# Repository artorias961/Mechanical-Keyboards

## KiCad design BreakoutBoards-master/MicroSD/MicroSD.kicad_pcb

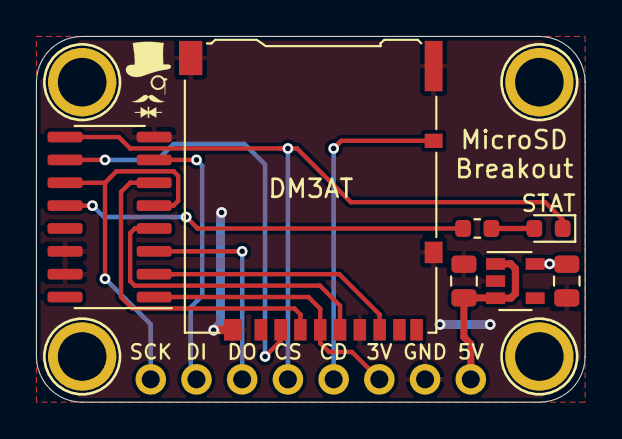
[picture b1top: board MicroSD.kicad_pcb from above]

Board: 2 copper layers, 30.5 x 20.3 mm, 12 parts (1 on the bottom side), 14 nets.

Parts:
C1, C2: 10uF; C_0805_2012Metric
DM3AT: Micro_SD_Card_Det; microSD_HC_Hirose_DM3AT-SF-PEJM5
H1, H2, H3, H4: MountingHole; MountingHole_M2.5_SirBoard
J1: Conn_01x08; PinHeader_1x08_P2.54mm_Vertical
R6: 1K; R_0603_1608Metric
STAT: LED; LED_0603_1608Metric
U1: AP2127K-3.3; SOT-23-5
U2: 4050; SOIC-16_3.9x9.9mm_P1.27mm

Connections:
/CLK_SD: DM3AT.5, U2.4
/CS_SD: DM3AT.2, U2.10
/DI_SD: DM3AT.3, U2.6
/DO_SD: DM3AT.7, U2.2
CS: J1.4, STAT.1, U2.9
DETA: DM3AT.10, J1.5
DI: J1.2, U2.7
DO: J1.3, U2.3
GND: C1.2, C2.2, DM3AT.6, DM3AT.11, J1.7, U1.2, U2.8, U2.14, U2.15
unnamed: R6.2, STAT.2
unnamed: R6.1, U2.12
SCK: J1.1, U2.5, U2.11
VIN: C1.1, J1.8, U1.1, U1.3
VOUT: C2.1, DM3AT.4, J1.6, U1.5, U2.1

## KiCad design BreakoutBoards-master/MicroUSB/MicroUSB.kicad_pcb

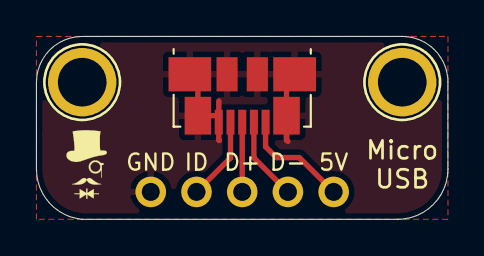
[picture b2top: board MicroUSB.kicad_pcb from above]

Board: 2 copper layers, 22.9 x 10.2 mm, 4 parts (1 on the bottom side), 5 nets.

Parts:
H1, H2: MountingHole; MountingHole_M2.5_SirBoard
J1: USB_B_Micro; USB_Micro-B_Molex_47346-0001
J2: Conn_01x05; PinHeader_1x05_P2.54mm_Vertical

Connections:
/D+: J1.3, J2.3
/D-: J1.2, J2.2
/GND: J1.5, J1.6, J2.5
/ID: J1.4, J2.4
/VBus: J1.1, J2.1

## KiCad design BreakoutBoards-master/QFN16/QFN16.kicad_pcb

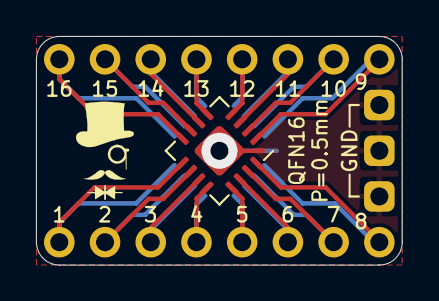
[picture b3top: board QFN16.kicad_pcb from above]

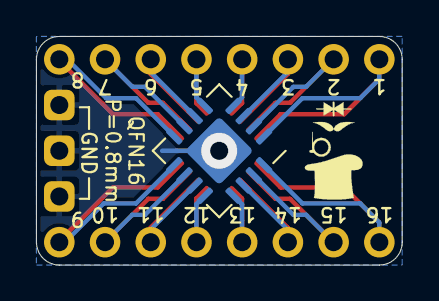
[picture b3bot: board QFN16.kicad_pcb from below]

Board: 2 copper layers, 20.3 x 12.7 mm, 5 parts (2 on the bottom side), 17 nets.

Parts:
J1, J3: Conn_01x08; PinHeader_1x08_P2.54mm_Vertical
J2: Conn_02x08_Counter_Clockwise; QFN-16-1EP_4x4mm_P0.65mm_EP2.1x2.1mm
J4: Conn_02x08_Counter_Clockwise; QFN-16-1EP_5x5mm_P0.8mm_EP2.7x2.7mm
J5: Conn_01x03; PinHeader_1x03_P2.54mm_Vertical

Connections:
unnamed: J1.1, J2.1, J4.8
unnamed: J1.2, J2.2, J4.7
unnamed: J1.3, J2.3, J4.6
unnamed: J1.4, J2.4, J4.5
unnamed: J1.5, J2.5, J4.4
unnamed: J1.6, J2.6, J4.3
unnamed: J1.7, J2.7, J4.2
unnamed: J1.8, J2.8, J4.1
unnamed: J2.9, J3.8, J4.16
unnamed: J2.10, J3.7, J4.15
unnamed: J2.11, J3.6, J4.14
unnamed: J2.12, J3.5, J4.13
unnamed: J2.13, J3.4, J4.12
unnamed: J2.14, J3.3, J4.11
unnamed: J2.15, J3.2, J4.10
unnamed: J2.16, J3.1, J4.9
unnamed: J2.17, J4.17, J5.1, J5.2, J5.3

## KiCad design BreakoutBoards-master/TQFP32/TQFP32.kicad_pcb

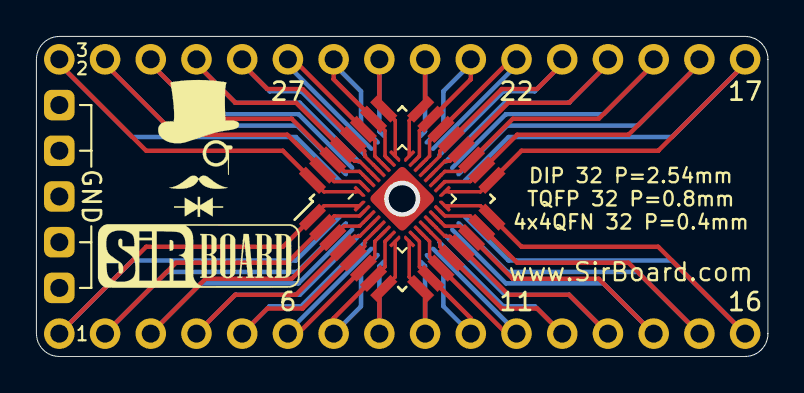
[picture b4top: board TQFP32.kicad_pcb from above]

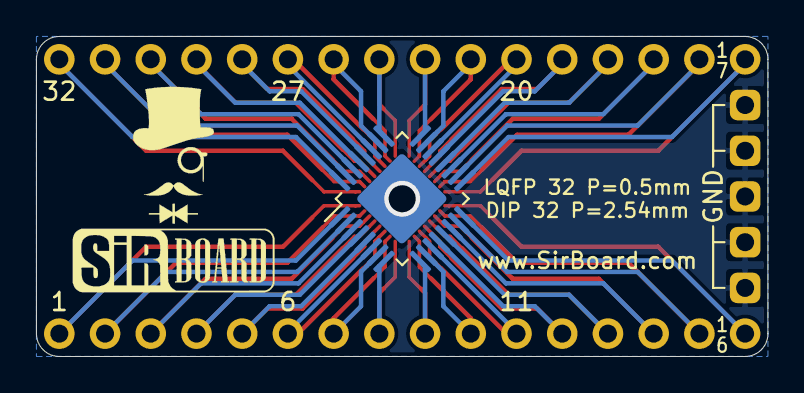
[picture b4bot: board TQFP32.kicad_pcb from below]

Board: 2 copper layers, 40.6 x 17.8 mm, 6 parts (3 on the bottom side), 33 nets.

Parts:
J1, J2: Conn_01x16; PinHeader_1x16_P2.54mm_Vertical
J3: Conn_02x16_Counter_Clockwise; TQFP-32_7x7mm_P0.8mm
J4: Conn_02x16_Counter_Clockwise; LQFP-32_5x5mm_P0.5mm
J5: Conn_02x16_Counter_Clockwise; QFN-32-1EP_4x4mm_P0.4mm_EP2.65x2.65mm
J6: Conn_01x05; PinHeader_1x05_P2.54mm_Vertical

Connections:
GND: J5.33, J6.1, J6.2, J6.3, J6.4, J6.5
unnamed: J1.1, J3.1, J4.16, J5.1
unnamed: J1.2, J3.2, J4.15, J5.2
unnamed: J1.3, J3.3, J4.14, J5.3
unnamed: J1.4, J3.4, J4.13, J5.4
unnamed: J1.5, J3.5, J4.12, J5.5
unnamed: J1.6, J3.6, J4.11, J5.6
unnamed: J1.7, J3.7, J4.10, J5.7
unnamed: J1.8, J3.8, J4.9, J5.8
unnamed: J1.9, J3.9, J4.8, J5.9
unnamed: J1.10, J3.10, J4.7, J5.10
unnamed: J1.11, J3.11, J4.6, J5.11
unnamed: J1.12, J3.12, J4.5, J5.12
unnamed: J1.13, J3.13, J4.4, J5.13
unnamed: J1.14, J3.14, J4.3, J5.14
unnamed: J1.15, J3.15, J4.2, J5.15
unnamed: J1.16, J3.16, J4.1, J5.16
unnamed: J2.1, J3.32, J4.17, J5.32
unnamed: J2.2, J3.31, J4.18, J5.31
unnamed: J2.3, J3.30, J4.19, J5.30
unnamed: J2.4, J3.29, J4.20, J5.29
unnamed: J2.5, J3.28, J4.21, J5.28
unnamed: J2.6, J3.27, J4.22, J5.27
unnamed: J2.7, J3.26, J4.23, J5.26
unnamed: J2.8, J3.25, J4.24, J5.25
unnamed: J2.9, J3.24, J4.25, J5.24
unnamed: J2.10, J3.23, J4.26, J5.23
unnamed: J2.11, J3.22, J4.27, J5.22
unnamed: J2.12, J3.21, J4.28, J5.21
unnamed: J2.13, J3.20, J4.29, J5.20
unnamed: J2.14, J3.19, J4.30, J5.19
unnamed: J2.15, J3.18, J4.31, J5.18
unnamed: J2.16, J3.17, J4.32, J5.17

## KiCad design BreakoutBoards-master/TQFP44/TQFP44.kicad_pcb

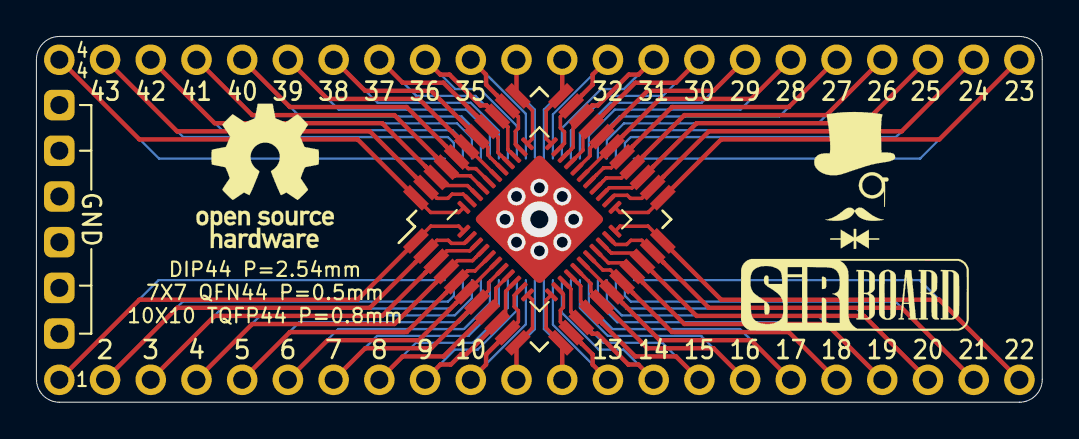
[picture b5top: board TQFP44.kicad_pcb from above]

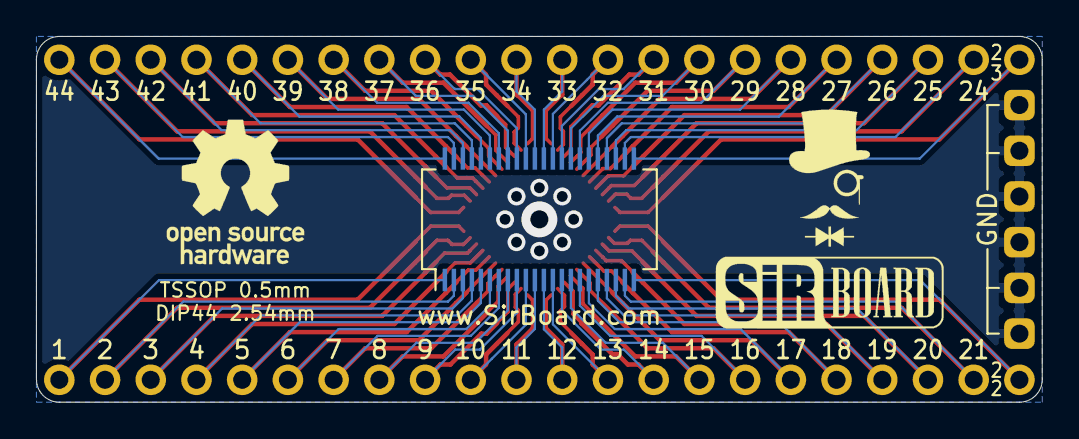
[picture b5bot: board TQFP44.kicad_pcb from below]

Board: 2 copper layers, 55.9 x 20.3 mm, 6 parts (2 on the bottom side), 45 nets.

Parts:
J1, J2: Conn_01x22; PinHeader_1x22_P2.54mm_Vertical
J3: Conn_02x22_Counter_Clockwise; TQFP-44_10x10mm_P0.8mm
J4: Conn_02x22_Counter_Clockwise; QFN-44-1EP_7x7mm_P0.5mm_EP5.15x5.15mm
J5: Conn_02x22_Counter_Clockwise; SSOP-44_5.3x12.8mm_P0.5mm
J6: Conn_01x06; PinHeader_1x06_P2.54mm_Vertical

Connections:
unnamed: J1.1, J3.44, J4.44, J5.23
unnamed: J1.2, J3.43, J4.43, J5.24
unnamed: J1.3, J3.42, J4.42, J5.25
unnamed: J1.4, J3.41, J4.41, J5.26
unnamed: J1.5, J3.40, J4.40, J5.27
unnamed: J1.6, J3.39, J4.39, J5.28
unnamed: J1.7, J3.38, J4.38, J5.29
unnamed: J1.8, J3.37, J4.37, J5.30
unnamed: J1.9, J3.36, J4.36, J5.31
unnamed: J1.10, J3.35, J4.35, J5.32
unnamed: J1.11, J3.34, J4.34, J5.33
unnamed: J1.12, J3.33, J4.33, J5.34
unnamed: J1.13, J3.32, J4.32, J5.35
unnamed: J1.14, J3.31, J4.31, J5.36
unnamed: J1.15, J3.30, J4.30, J5.37
unnamed: J1.16, J3.29, J4.29, J5.38
unnamed: J1.17, J3.28, J4.28, J5.39
unnamed: J1.18, J3.27, J4.27, J5.40
unnamed: J1.19, J3.26, J4.26, J5.41
unnamed: J1.20, J3.25, J4.25, J5.42
unnamed: J1.21, J3.24, J4.24, J5.43
unnamed: J1.22, J3.23, J4.23, J5.44
unnamed: J2.1, J3.1, J4.1, J5.22
unnamed: J2.2, J3.2, J4.2, J5.21
unnamed: J2.3, J3.3, J4.3, J5.20
unnamed: J2.4, J3.4, J4.4, J5.19
unnamed: J2.5, J3.5, J4.5, J5.18
unnamed: J2.6, J3.6, J4.6, J5.17
unnamed: J2.7, J3.7, J4.7, J5.16
unnamed: J2.8, J3.8, J4.8, J5.15
unnamed: J2.9, J3.9, J4.9, J5.14
unnamed: J2.10, J3.10, J4.10, J5.13
unnamed: J2.11, J3.11, J4.11, J5.12
unnamed: J2.12, J3.12, J4.12, J5.11
unnamed: J2.13, J3.13, J4.13, J5.10
unnamed: J2.14, J3.14, J4.14, J5.9
unnamed: J2.15, J3.15, J4.15, J5.8
unnamed: J2.16, J3.16, J4.16, J5.7
unnamed: J2.17, J3.17, J4.17, J5.6
unnamed: J2.18, J3.18, J4.18, J5.5
unnamed: J2.19, J3.19, J4.19, J5.4
unnamed: J2.20, J3.20, J4.20, J5.3
unnamed: J2.21, J3.21, J4.21, J5.2
unnamed: J2.22, J3.22, J4.22, J5.1
unnamed: J4.45, J6.1, J6.2, J6.3, J6.4, J6.5, J6.6

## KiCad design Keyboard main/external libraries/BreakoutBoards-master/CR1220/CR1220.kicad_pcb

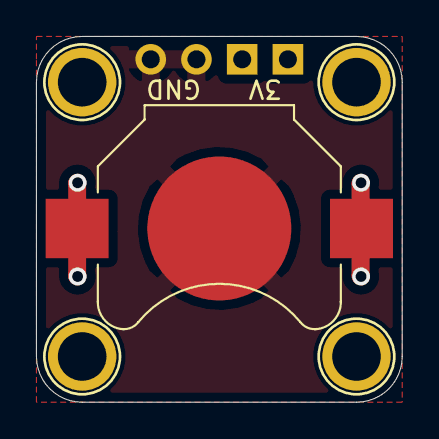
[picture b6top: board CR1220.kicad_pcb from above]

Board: 2 copper layers, 20.3 x 20.3 mm, 6 parts (0 on the bottom side), 2 nets.

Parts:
BT1: Battery_Cell; BatteryHolder_Keystone_3000_1x12mm
H1, H2, H3, H4: MountingHole; MountingHole_M2.5_SirBoard
J1: Conn_01x04; PinHeader_1x04_P2.54mm_Vertical

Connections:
+3V0: BT1.1, J1.1, J1.2
GND: BT1.2, J1.3, J1.4

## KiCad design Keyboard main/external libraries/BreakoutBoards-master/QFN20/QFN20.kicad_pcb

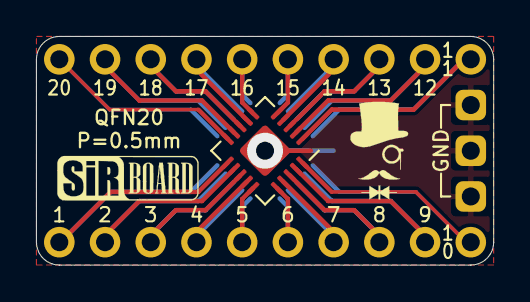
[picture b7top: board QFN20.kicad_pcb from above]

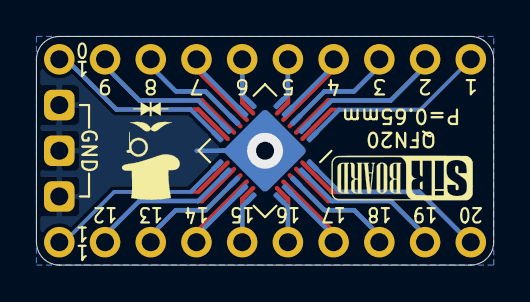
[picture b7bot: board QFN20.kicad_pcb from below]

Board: 2 copper layers, 25.4 x 12.7 mm, 5 parts (2 on the bottom side), 21 nets.

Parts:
J1, J3: Conn_01x10; PinHeader_1x10_P2.54mm_Vertical
J2: Conn_02x10_Counter_Clockwise; QFN-20-1EP_4x4mm_P0.5mm_EP2.5x2.5mm
J4: Conn_02x10_Counter_Clockwise; QFN-20-1EP_5x5mm_P0.65mm_EP3.35x3.35mm
J5: Conn_01x03; PinHeader_1x03_P2.54mm_Vertical

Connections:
unnamed: J1.1, J2.1, J4.10
unnamed: J1.2, J2.2, J4.9
unnamed: J1.3, J2.3, J4.8
unnamed: J1.4, J2.4, J4.7
unnamed: J1.5, J2.5, J4.6
unnamed: J1.6, J2.6, J4.5
unnamed: J1.7, J2.7, J4.4
unnamed: J1.8, J2.8, J4.3
unnamed: J1.9, J2.9, J4.2
unnamed: J1.10, J2.10, J4.1
unnamed: J2.11, J3.10, J4.20
unnamed: J2.12, J3.9, J4.19
unnamed: J2.13, J3.8, J4.18
unnamed: J2.14, J3.7, J4.17
unnamed: J2.15, J3.6, J4.16
unnamed: J2.16, J3.5, J4.15
unnamed: J2.17, J3.4, J4.14
unnamed: J2.18, J3.3, J4.13
unnamed: J2.19, J3.2, J4.12
unnamed: J2.20, J3.1, J4.11
unnamed: J2.21, J4.21, J5.1, J5.2, J5.3

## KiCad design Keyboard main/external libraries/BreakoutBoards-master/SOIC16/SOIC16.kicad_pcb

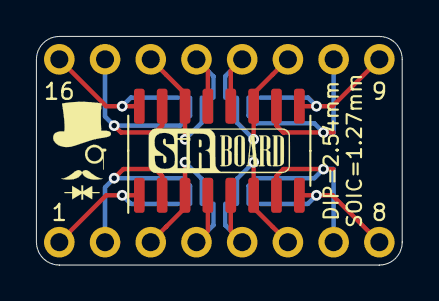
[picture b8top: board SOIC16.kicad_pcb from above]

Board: 2 copper layers, 20.3 x 12.7 mm, 3 parts (0 on the bottom side), 16 nets.

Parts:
J1: Conn_02x08_Counter_Clockwise; SOIC-16_3.9x9.9mm_P1.27mm
J2, J3: Conn_01x08; PinHeader_1x08_P2.54mm_Vertical

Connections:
unnamed: J1.1, J3.1
unnamed: J1.2, J3.2
unnamed: J1.3, J3.3
unnamed: J1.4, J3.4
unnamed: J1.5, J3.5
unnamed: J1.6, J3.6
unnamed: J1.7, J3.7
unnamed: J1.8, J3.8
unnamed: J1.9, J2.8
unnamed: J1.10, J2.7
unnamed: J1.11, J2.6
unnamed: J1.12, J2.5
unnamed: J1.13, J2.4
unnamed: J1.14, J2.3
unnamed: J1.15, J2.2
unnamed: J1.16, J2.1
